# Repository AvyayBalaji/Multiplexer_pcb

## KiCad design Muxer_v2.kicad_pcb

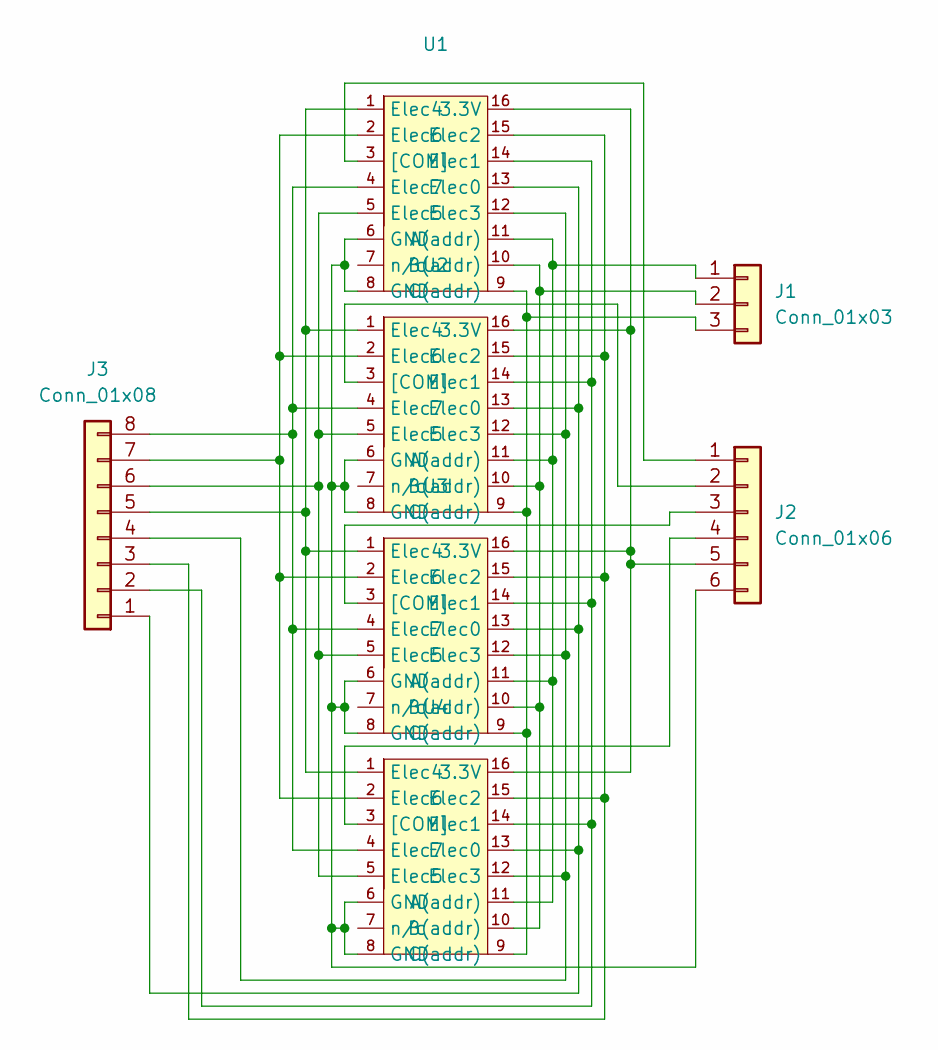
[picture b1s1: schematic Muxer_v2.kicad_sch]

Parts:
J1: Conn_01x03; PinHeader_1x03_P2.54mm_Vertical
J2: Conn_01x06; PinHeader_1x06_P2.54mm_Vertical
J3: Conn_01x08; PinHeader_1x08_P2.54mm_Vertical
U1, U2, U3, U4: MAX4617_MODULE

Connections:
unnamed: J1.1 (A), U1.11 (A(addr)), U2.11 (A(addr)), U3.11 (A(addr)), U4.11 (A(addr))
unnamed: J1.2 (B), U1.10 (B(addr)), U2.10 (B(addr)), U3.10 (B(addr)), U4.10 (B(addr))
unnamed: J1.3 (C), U1.9 (C(addr)), U2.9 (C(addr)), U3.9 (C(addr)), U4.9 (C(addr))
unnamed: J2.5 (3.3_V), U1.16 (3.3V), U2.16 (3.3V), U3.16 (3.3V), U4.16 (3.3V)
unnamed: J2.1 (F+), U1.3 ([COM])
unnamed: J2.2 (F-), U2.3 ([COM])
unnamed: J2.6 (GND), U1.6 (GND), U1.8 (GND), U2.6 (GND), U2.8 (GND), U3.6 (GND), U3.8 (GND), U4.6 (GND), U4.8 (GND)
unnamed: J2.3 (S+), U3.3 ([COM])
unnamed: J2.4 (S-), U4.3 ([COM])
unnamed: J3.1, U1.13 (Elec0), U2.13 (Elec0), U3.13 (Elec0), U4.13 (Elec0)
unnamed: J3.2, U1.14 (Elec1), U2.14 (Elec1), U3.14 (Elec1), U4.14 (Elec1)
unnamed: J3.3, U1.15 (Elec2), U2.15 (Elec2), U3.15 (Elec2), U4.15 (Elec2)
unnamed: J3.4, U1.12 (Elec3), U2.12 (Elec3), U3.12 (Elec3), U4.12 (Elec3)
unnamed: J3.5, U1.1 (Elec4), U2.1 (Elec4), U3.1 (Elec4), U4.1 (Elec4)
unnamed: J3.6, U1.5 (Elec5), U2.5 (Elec5), U3.5 (Elec5), U4.5 (Elec5)
unnamed: J3.7, U1.2 (Elec6), U2.2 (Elec6), U3.2 (Elec6), U4.2 (Elec6)
unnamed: J3.8, U1.4 (Elec7), U2.4 (Elec7), U3.4 (Elec7), U4.4 (Elec7)

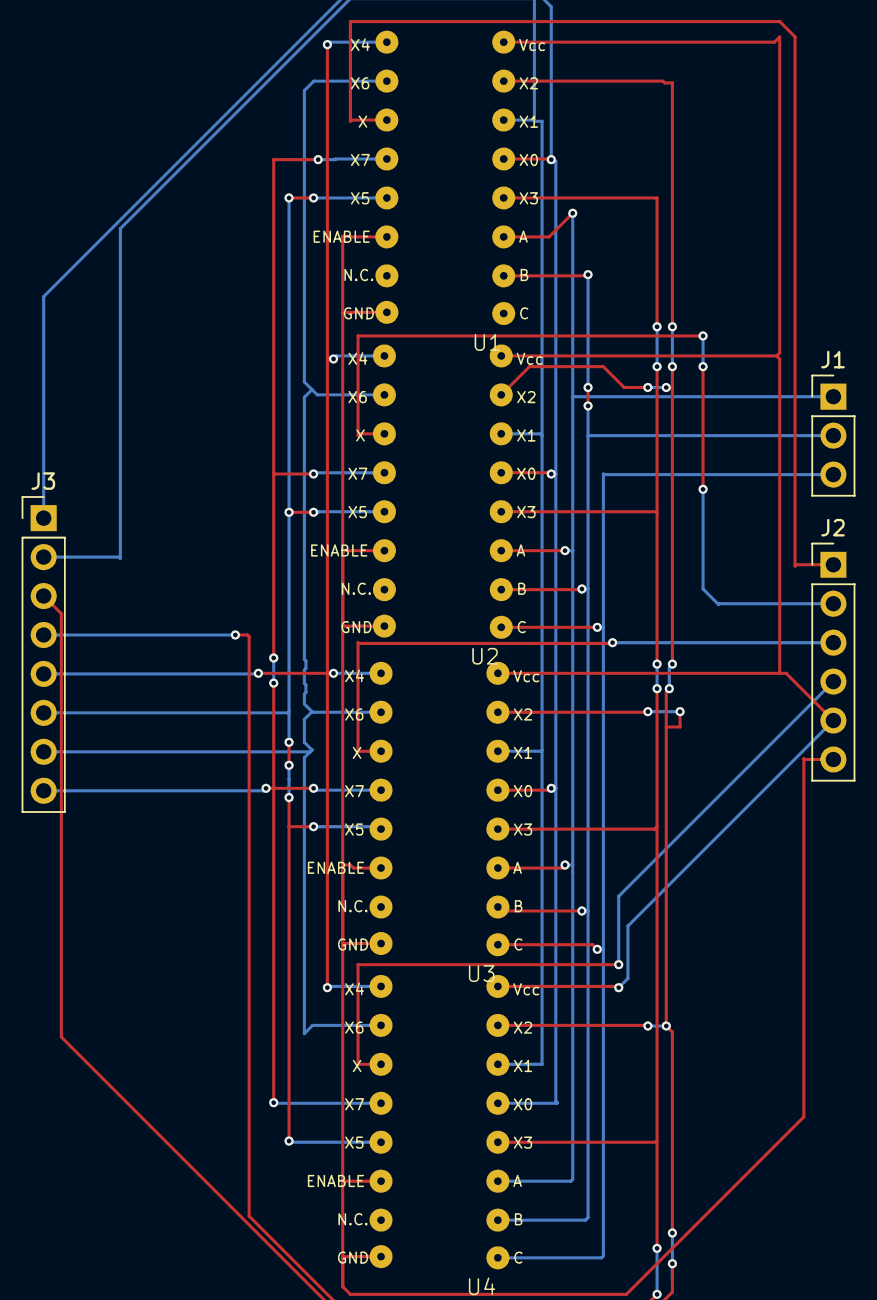
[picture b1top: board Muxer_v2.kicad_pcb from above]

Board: 2 copper layers, 7 parts (0 on the bottom side), 17 nets.

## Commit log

2026-03-31 Initial commit of muxer
2026-03-31 Remade 6-pin connector footprint, added it to schematic file
2026-03-31 Removed COnnector_6 footprint due to redundancy
2026-03-31 Removed untitled file from multiplexer footprint folder
2026-04-03 Started electrode wire connections, attached 6-pin connector to input areas
2026-04-07 Adjusted pin orientations on Multiplexer symbol
2026-04-07 Configured multiplexer setup, added 8 and 3 pin connectors
2026-04-07 Started pcb creation, placed 3.3V and electrode inputs
2026-04-09 Finished wiring using vias
2026-04-09 Added rectangle surrounding pcb
2026-04-09 Updating pro file to reflect changes in all other files
